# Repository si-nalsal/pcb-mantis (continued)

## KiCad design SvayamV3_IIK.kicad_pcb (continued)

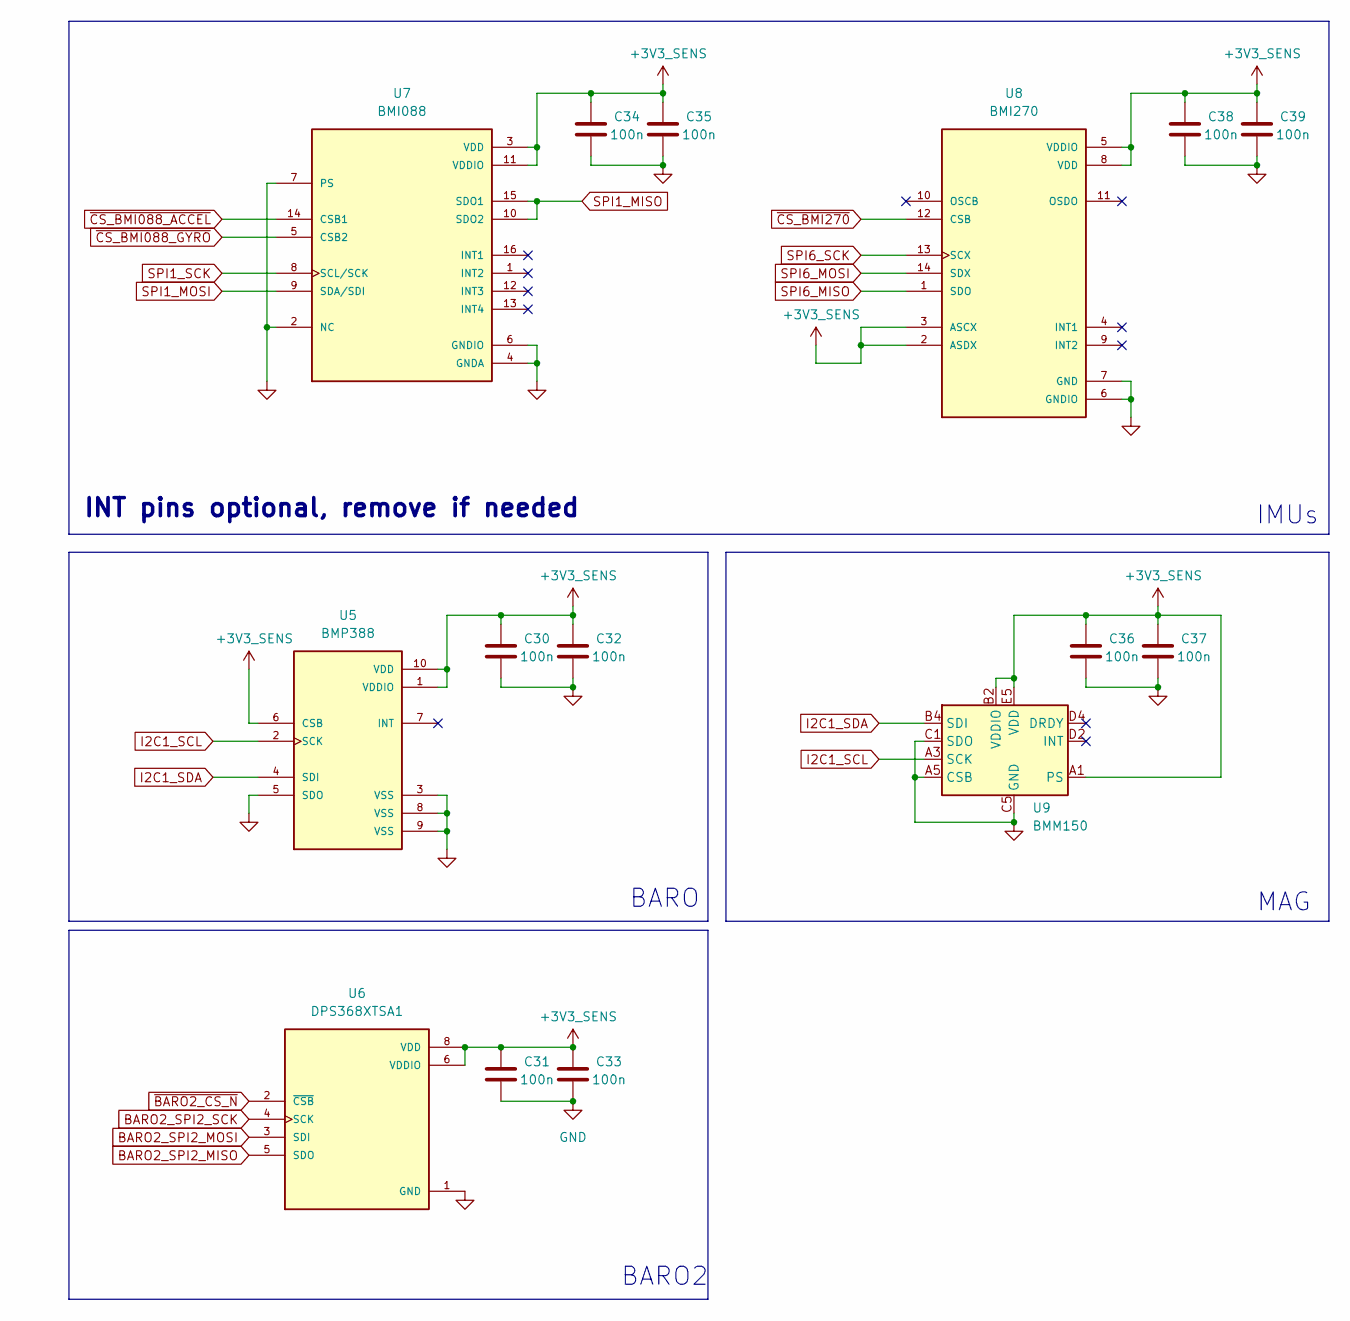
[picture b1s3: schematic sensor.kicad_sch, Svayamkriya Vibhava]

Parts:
C30, C31, C32, C33, C34, C35, C36, C37, C38, C39: 100n; C_0402_1005Metric; MPN CL05B104KB54PNC; LCSC C307331
U5: BMP388; XDCR_BMP388; PARTREV 1.1; LCSC C779278
U6: DPS368XTSA1; XDCR_DPS310XTSA1; MPN DPS368XTSA1; LCSC C3232508
U7: BMI088; PQFN50P450X300X100-16N; MPN BMI088; LCSC C194919
U8: BMI270; XDCR_BMI270; MPN BMI270; LCSC C2836813
U9: BMM150; WLCSP-12_1.56x1.56mm_P0.4mm; MPN BMM150; LCSC C171681

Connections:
+3V3_SENS: C30.1, C31.1, C32.1, C33.1, C34.1, C35.1, C36.1, C37.1, C38.1, C39.1, U5.1 (VDDIO), U5.6 (CSB), U5.10 (VDD), U6.6 (VDDIO), U6.8 (VDD), U7.3 (VDD), U7.11 (VDDIO), U8.2 (ASDX), U8.3 (ASCX), U8.5 (VDDIO), U8.8 (VDD), U9.A1 (PS), U9.B2 (VDDIO), U9.E5 (VDD); also elsewhere on the board
BARO2_SPI2_MISO: U6.5 (SDO); also elsewhere on the board
BARO2_SPI2_MOSI: U6.3 (SDI); also elsewhere on the board
BARO2_SPI2_SCK: U6.4 (SCK); also elsewhere on the board
GND: C30.2, C31.2, C32.2, C33.2, C34.2, C35.2, C36.2, C37.2, C38.2, C39.2, U5.3 (VSS), U5.5 (SDO), U5.8 (VSS), U5.9 (VSS), U6.1 (GND), U6.7 (GND), U7.2 (NC), U7.4 (GNDA), U7.6 (GNDIO), U7.7 (PS), U8.6 (GNDIO), U8.7 (GND), U9.A5 (CSB), U9.C1 (SDO), U9.C5 (GND), U9.E1 (GND), U9.E3 (GND); also elsewhere on the board
I2C1_SCL: U5.2 (SCK), U9.A3 (SCK); also elsewhere on the board
I2C1_SDA: U5.4 (SDI), U9.B4 (SDI); also elsewhere on the board
SPI1_MISO: U7.10 (SDO2), U7.15 (SDO1); also elsewhere on the board
SPI1_MOSI: U7.9 (SDA/SDI); also elsewhere on the board
SPI1_SCK: U7.8 (SCL/SCK); also elsewhere on the board
SPI6_MISO: U8.1 (SDO); also elsewhere on the board
SPI6_MOSI: U8.14 (SDX); also elsewhere on the board
SPI6_SCK: U8.13 (SCX); also elsewhere on the board
~BARO2_CS_N: U6.2 (~CSB); also elsewhere on the board
~CS_BMI088_ACCEL: U7.14 (CSB1); also elsewhere on the board
~CS_BMI088_GYRO: U7.5 (CSB2); also elsewhere on the board
~CS_BMI270: U8.12 (CSB); also elsewhere on the board

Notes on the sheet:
MAG
BARO2
IMUs
BARO
INT pins optional, remove if needed

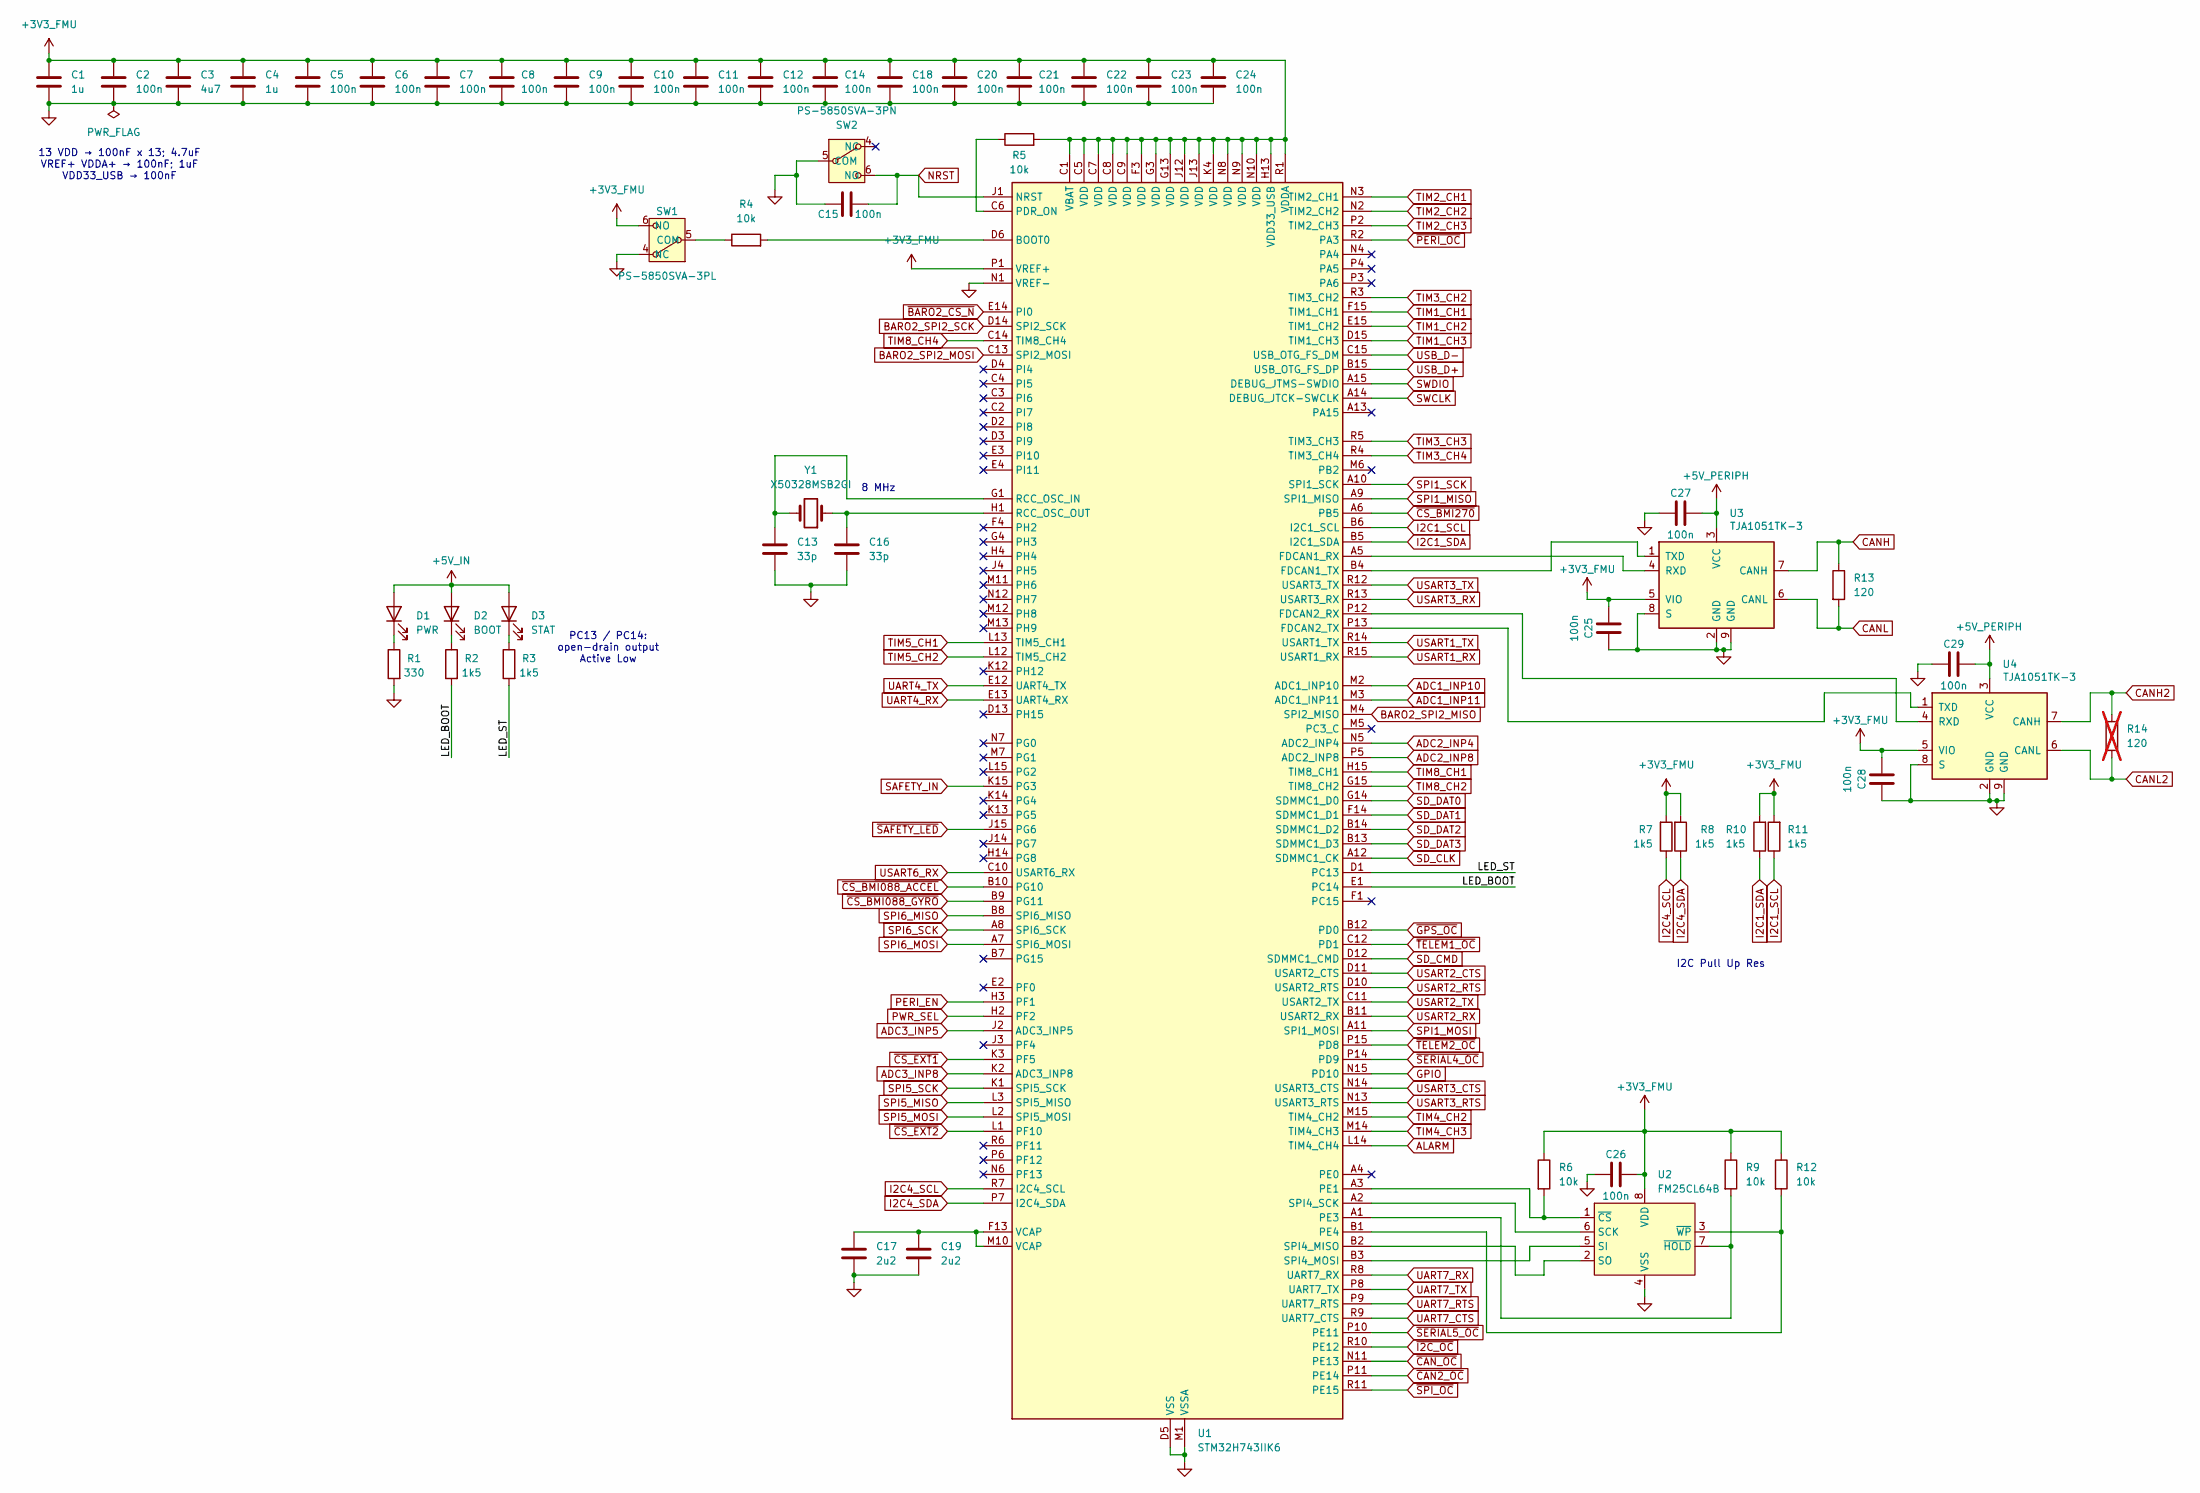
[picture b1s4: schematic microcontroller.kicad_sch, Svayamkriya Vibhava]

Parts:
C1, C4: 1u; C_0603_1608Metric; MPN CL10A105KB8NNNC; LCSC C15849
C2, C5, C6, C7, C8, C9, C10, C11, C12, C14, C15, C18, C20, C21, C22, C23, C24, C25, C26, C27, C28, C29: 100n; C_0402_1005Metric; MPN CL05B104KB54PNC; LCSC C307331
C3: 4u7; C_0603_1608Metric; MPN CL10A475KO8NNNC; LCSC C19666
C13, C16: 33p; C_0402_1005Metric; MPN 0402CG330J500NT; LCSC C1562
C17, C19: 2u2; C_0603_1608Metric; MPN CL10A225KO8NNNC; LCSC C23630
D1: PWR; D_0603_1608Metric; MPN NCD0603R1; LCSC C84263
D2: BOOT; D_0603_1608Metric; MPN NCD0603R1; LCSC C84263
D3: STAT; D_0603_1608Metric; MPN NCD0603R1; LCSC C84263
R1: 330; R_0402_1005Metric; MPN 0402WGF3300TCE; LCSC C25104
R2, R3, R7, R8, R10, R11: 1k5; R_0402_1005Metric; MPN 0402WGF1501TCE; LCSC C25867
R4, R5, R6, R9, R12: 10k; R_0402_1005Metric; MPN 0402WGF1002TCE; LCSC C25744
R13: 120; R_0402_1005Metric; MPN 0402WGF1200TCE; LCSC C25079
R14: 120; R_0402_1005Metric; MPN 0402WGF1200TCE; LCSC C25079; not fitted
SW1: PS-5850SVA-3PL; SW-SMD_G-SWITCH_PS-5850SVX-3PL; MPN PS-5850SVA-3PL; LCSC C5155594
SW2: PS-5850SVA-3PN; SW-SMD_G-SWITCH_PS-5850SVX-3PL; MPN PS-5850SVA-3PN; LCSC C5155595
U1: STM32H743IIK6; UFBGA-201_10x10mm_Layout15x15_P0.65mm; MPN STM32H743IIK6; LCSC C129442
U2: FM25CL64B; SOIC-8_3.9x4.9mm_P1.27mm; MPN FM25CL64B-GTR; LCSC C9830
U3, U4: TJA1051TK-3; DFN-8-1EP_3x3mm_P0.65mm_EP1.55x2.4mm; MPN TJA1051TK/3,118; LCSC C124020
Y1: X50328MSB2GI; Crystal_SMD_5032-2Pin_5.0x3.2mm; MPN X50328MSB2GI; LCSC C115962

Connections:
+3V3_FMU: C1.1, C2.1, C3.1, C4.1, C5.1, C6.1, C7.1, C8.1, C9.1, C10.1, C11.1, C12.1, C14.1, C18.1, C20.1, C21.1, C22.1, C23.1, C24.1, C25.1, C26.2, C28.1, R5.2, R6.1, R7.2, R8.2, R9.1, R10.2, R11.2, R12.1, SW1.6 (NO), U1.C1 (VBAT), U1.C5 (VDD), U1.C7 (VDD), U1.C8 (VDD), U1.C9 (VDD), U1.F3 (VDD), U1.G3 (VDD), U1.G13 (VDD), U1.H13 (VDD33_USB), U1.J12 (VDD), U1.J13 (VDD), U1.K4 (VDD), U1.N8 (VDD), U1.N9 (VDD), U1.N10 (VDD), U1.P1 (VREF+), U1.R1 (VDDA), U2.8 (VDD), U3.5 (VIO), U4.5 (VIO); also elsewhere on the board
+5V_IN: D1.2 (A), D2.2 (A), D3.2 (A); also elsewhere on the board
+5V_PERIPH: C27.2, C29.2, U3.3 (VCC), U4.3 (VCC); also elsewhere on the board
/Microcontroller/LED_BOOT: R2.2, U1.E1 (PC14)
/Microcontroller/LED_ST: R3.2, U1.D1 (PC13)
ADC1_INP10: U1.M2 (ADC1_INP10); also elsewhere on the board
ADC1_INP11: U1.M3 (ADC1_INP11); also elsewhere on the board
ADC2_INP4: U1.N5 (ADC2_INP4); also elsewhere on the board
ADC2_INP8: U1.P5 (ADC2_INP8); also elsewhere on the board
ADC3_INP5: U1.J2 (ADC3_INP5); also elsewhere on the board
ADC3_INP8: U1.K2 (ADC3_INP8); also elsewhere on the board
ALARM: U1.L14 (TIM4_CH4); also elsewhere on the board
BARO2_SPI2_MISO: U1.M4 (SPI2_MISO); also elsewhere on the board
BARO2_SPI2_MOSI: U1.C13 (SPI2_MOSI); also elsewhere on the board
BARO2_SPI2_SCK: U1.D14 (SPI2_SCK); also elsewhere on the board
CANH: R13.1, U3.7 (CANH); also elsewhere on the board
CANH2: R14.1, U4.7 (CANH); also elsewhere on the board
CANL: R13.2, U3.6 (CANL); also elsewhere on the board
CANL2: R14.2, U4.6 (CANL); also elsewhere on the board
GND: C1.2, C2.2, C3.2, C4.2, C5.2, C6.2, C7.2, C8.2, C9.2, C10.2, C11.2, C12.2, C13.2, C14.2, C15.1, C16.2, C17.2, C18.2, C19.2, C20.2, C21.2, C22.2, C23.2, C24.2, C25.2, C26.1, C27.1, C28.2, C29.1, R1.2, SW1.4 (NC), SW2.5 (COM), U1.D5 (VSS), U1.D7 (VSS), U1.D8 (VSS), U1.D9 (VSS), U1.F2 (VSS), U1.F6 (VSS), U1.F7 (VSS), U1.F8 (VSS), U1.F9 (VSS), U1.F10 (VSS), U1.F12 (VSS), U1.G2 (VSS), U1.G6 (VSS), U1.G7 (VSS), U1.G8 (VSS), U1.G9 (VSS), U1.G10 (VSS), U1.G12 (VSS), U1.H6 (VSS), U1.H7 (VSS), U1.H8 (VSS), U1.H9 (VSS), U1.H10 (VSS), U1.H12 (VSS), U1.J6 (VSS), U1.J7 (VSS), U1.J8 (VSS), U1.J9 (VSS), U1.J10 (VSS), U1.K6 (VSS), U1.K7 (VSS), U1.K8 (VSS), U1.K9 (VSS), U1.K10 (VSS), U1.L4 (VSS), U1.M1 (VSSA), U1.M8 (VSS), U1.M9 (VSS), U1.N1 (VREF-), U2.4 (VSS), U3.2 (GND), U3.8 (S), U3.9 (GND), U4.2 (GND), U4.8 (S), U4.9 (GND); also elsewhere on the board
GPIO: U1.N15 (PD10); also elsewhere on the board
I2C1_SCL: R11.1, U1.B6 (I2C1_SCL); also elsewhere on the board
I2C1_SDA: R10.1, U1.B5 (I2C1_SDA); also elsewhere on the board
I2C4_SCL: R7.1, U1.R7 (I2C4_SCL); also elsewhere on the board
I2C4_SDA: R8.1, U1.P7 (I2C4_SDA); also elsewhere on the board
NRST: C15.2, SW2.6 (NO), U1.J1 (NRST); also elsewhere on the board
unnamed: C17.1, C19.1, U1.F13 (VCAP), U1.M10 (VCAP)
unnamed: D1.1 (K), R1.1
unnamed: D2.1 (K), R2.1
unnamed: D3.1 (K), R3.1
unnamed: R4.1, SW1.5 (COM)
unnamed: R4.2, U1.D6 (BOOT0)
unnamed: U1.A5 (FDCAN1_RX), U3.4 (RXD)
unnamed: U1.B4 (FDCAN1_TX), U3.1 (TXD)
unnamed: U1.P12 (FDCAN2_RX), U4.4 (RXD)
unnamed: U1.P13 (FDCAN2_TX), U4.1 (TXD)
unnamed: R5.1, U1.C6 (PDR_ON)
unnamed: R6.2, U1.A3 (PE1), U2.1 (~CS)
unnamed: U1.A2 (SPI4_SCK), U2.6 (SCK)
unnamed: R9.2, U1.A1 (PE3), U2.7 (~HOLD)
unnamed: R12.2, U1.B1 (PE4), U2.3 (~WP)
unnamed: U1.B2 (SPI4_MISO), U2.2 (SO)
unnamed: U1.B3 (SPI4_MOSI), U2.5 (SI)
unnamed: C13.1, U1.G1 (RCC_OSC_IN), Y1.2
unnamed: C16.1, U1.H1 (RCC_OSC_OUT), Y1.1
PERI_EN: U1.H3 (PF1); also elsewhere on the board
PWR_SEL: U1.H2 (PF2); also elsewhere on the board
SAFETY_IN: U1.K15 (PG3); also elsewhere on the board
SD_CLK: U1.A12 (SDMMC1_CK); also elsewhere on the board
SD_CMD: U1.D12 (SDMMC1_CMD); also elsewhere on the board
SD_DAT0: U1.G14 (SDMMC1_D0); also elsewhere on the board
SD_DAT1: U1.F14 (SDMMC1_D1); also elsewhere on the board
SD_DAT2: U1.B14 (SDMMC1_D2); also elsewhere on the board
SD_DAT3: U1.B13 (SDMMC1_D3); also elsewhere on the board
SPI1_MISO: U1.A9 (SPI1_MISO); also elsewhere on the board
SPI1_MOSI: U1.A11 (SPI1_MOSI); also elsewhere on the board
SPI1_SCK: U1.A10 (SPI1_SCK); also elsewhere on the board
SPI5_MISO: U1.L3 (SPI5_MISO); also elsewhere on the board
SPI5_MOSI: U1.L2 (SPI5_MOSI); also elsewhere on the board
SPI5_SCK: U1.K1 (SPI5_SCK); also elsewhere on the board
SPI6_MISO: U1.B8 (SPI6_MISO); also elsewhere on the board
SPI6_MOSI: U1.A7 (SPI6_MOSI); also elsewhere on the board
SPI6_SCK: U1.A8 (SPI6_SCK); also elsewhere on the board
SWCLK: U1.A14 (DEBUG_JTCK-SWCLK); also elsewhere on the board
SWDIO: U1.A15 (DEBUG_JTMS-SWDIO); also elsewhere on the board
TIM1_CH1: U1.F15 (TIM1_CH1); also elsewhere on the board
TIM1_CH2: U1.E15 (TIM1_CH2); also elsewhere on the board
TIM1_CH3: U1.D15 (TIM1_CH3); also elsewhere on the board
TIM2_CH1: U1.N3 (TIM2_CH1); also elsewhere on the board
TIM2_CH2: U1.N2 (TIM2_CH2); also elsewhere on the board
TIM2_CH3: U1.P2 (TIM2_CH3); also elsewhere on the board
TIM3_CH2: U1.R3 (TIM3_CH2); also elsewhere on the board
TIM3_CH3: U1.R5 (TIM3_CH3); also elsewhere on the board
TIM3_CH4: U1.R4 (TIM3_CH4); also elsewhere on the board
TIM4_CH2: U1.M15 (TIM4_CH2); also elsewhere on the board
TIM4_CH3: U1.M14 (TIM4_CH3); also elsewhere on the board
TIM5_CH1: U1.L13 (TIM5_CH1); also elsewhere on the board
TIM5_CH2: U1.L12 (TIM5_CH2); also elsewhere on the board
TIM8_CH1: U1.H15 (TIM8_CH1); also elsewhere on the board
TIM8_CH2: U1.G15 (TIM8_CH2); also elsewhere on the board
TIM8_CH4: U1.C14 (TIM8_CH4); also elsewhere on the board
UART4_RX: U1.E13 (UART4_RX); also elsewhere on the board
UART4_TX: U1.E12 (UART4_TX); also elsewhere on the board
UART7_CTS: U1.R9 (UART7_CTS); also elsewhere on the board
UART7_RTS: U1.P9 (UART7_RTS); also elsewhere on the board
UART7_RX: U1.R8 (UART7_RX); also elsewhere on the board
UART7_TX: U1.P8 (UART7_TX); also elsewhere on the board
USART1_RX: U1.R15 (USART1_RX); also elsewhere on the board
USART1_TX: U1.R14 (USART1_TX); also elsewhere on the board
USART2_CTS: U1.D11 (USART2_CTS); also elsewhere on the board
USART2_RTS: U1.D10 (USART2_RTS); also elsewhere on the board
USART2_RX: U1.B11 (USART2_RX); also elsewhere on the board
USART2_TX: U1.C11 (USART2_TX); also elsewhere on the board
USART3_CTS: U1.N14 (USART3_CTS); also elsewhere on the board
USART3_RTS: U1.N13 (USART3_RTS); also elsewhere on the board
USART3_RX: U1.R13 (USART3_RX); also elsewhere on the board
USART3_TX: U1.R12 (USART3_TX); also elsewhere on the board
USART6_RX: U1.C10 (USART6_RX); also elsewhere on the board
USB_D+: U1.B15 (USB_OTG_FS_DP); also elsewhere on the board
USB_D-: U1.C15 (USB_OTG_FS_DM); also elsewhere on the board
~BARO2_CS_N: U1.E14 (PI0); also elsewhere on the board
~CAN2_OC: U1.P11 (PE14); also elsewhere on the board
~CAN_OC: U1.N11 (PE13); also elsewhere on the board
~CS_BMI088_ACCEL: U1.B10 (PG10); also elsewhere on the board
~CS_BMI088_GYRO: U1.B9 (PG11); also elsewhere on the board
~CS_BMI270: U1.A6 (PB5); also elsewhere on the board
~CS_EXT1: U1.K3 (PF5); also elsewhere on the board
~CS_EXT2: U1.L1 (PF10); also elsewhere on the board
~GPS_OC: U1.B12 (PD0); also elsewhere on the board
~I2C_OC: U1.R10 (PE12); also elsewhere on the board
~PERI_OC: U1.R2 (PA3); also elsewhere on the board
~SAFETY_LED: U1.J15 (PG6); also elsewhere on the board
~SERIAL4_OC: U1.P14 (PD9); also elsewhere on the board
~SERIAL5_OC: U1.P10 (PE11); also elsewhere on the board
~SPI_OC: U1.R11 (PE15); also elsewhere on the board
~TELEM1_OC: U1.C12 (PD1); also elsewhere on the board
~TELEM2_OC: U1.P15 (PD8); also elsewhere on the board

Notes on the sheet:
8 MHz
I2C Pull Up Res
13 VDD → 100nF x 13; 4.7uF VREF+ VDDA+ → 100nF; 1uF VDD33_USB → 100nF
PC13 / PC14: open-drain output Active Low

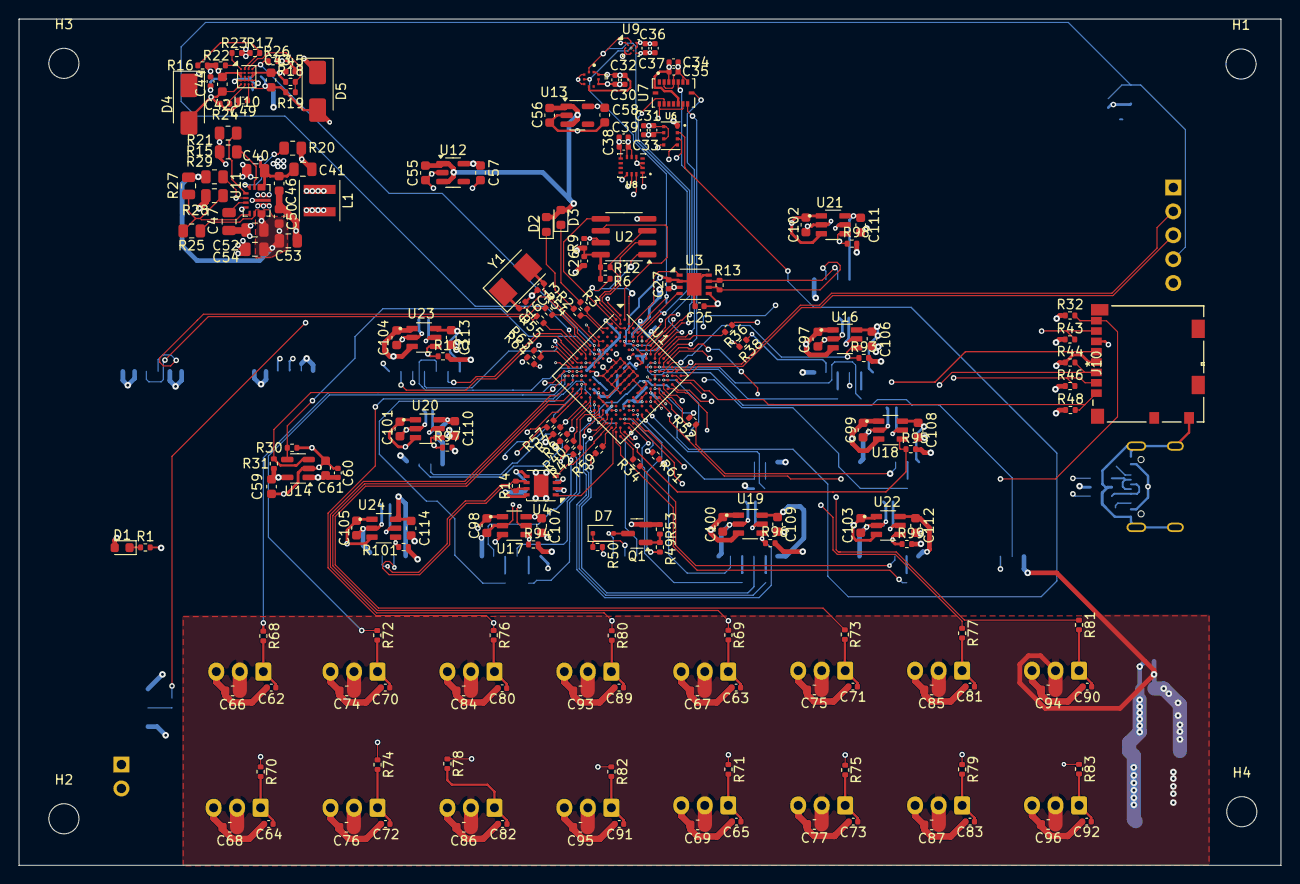
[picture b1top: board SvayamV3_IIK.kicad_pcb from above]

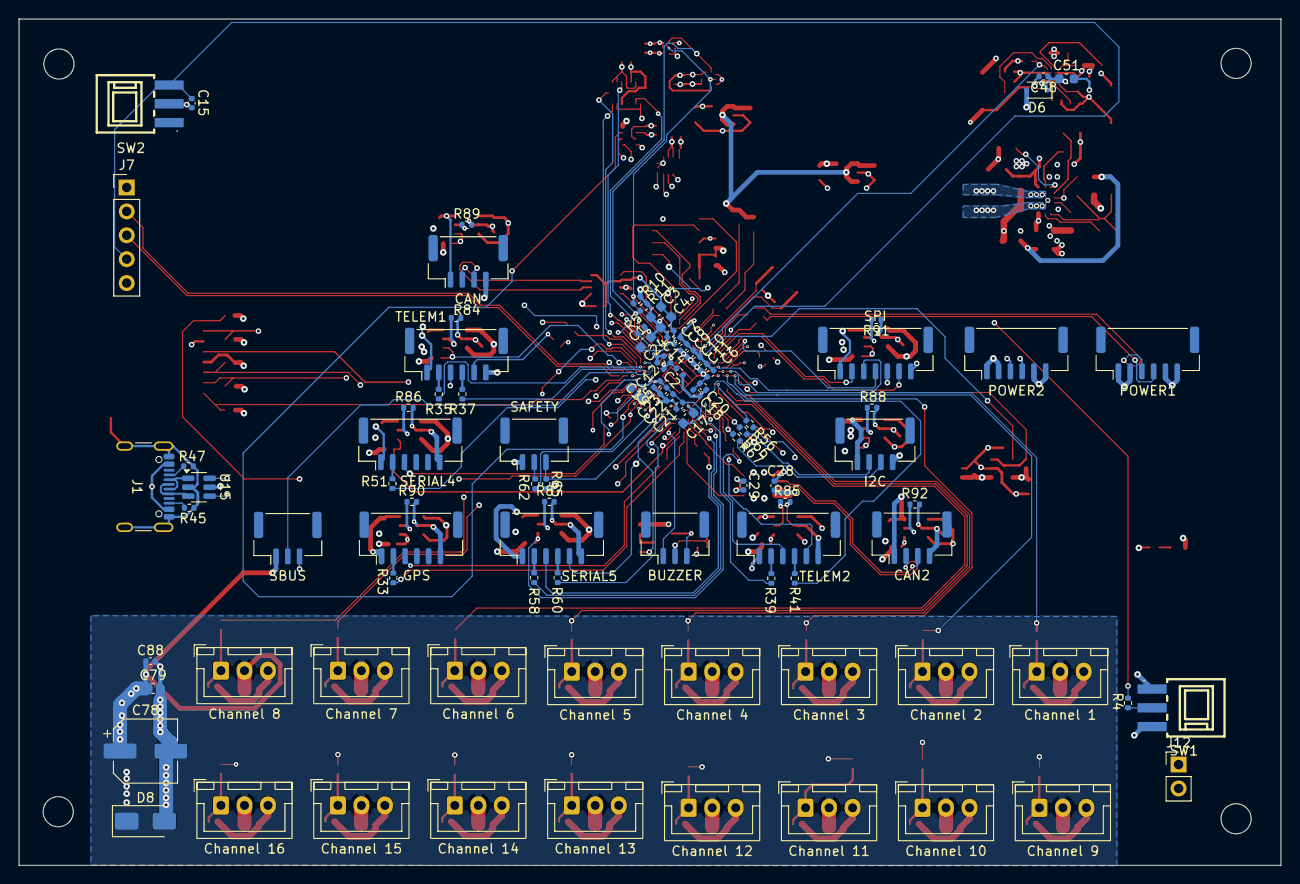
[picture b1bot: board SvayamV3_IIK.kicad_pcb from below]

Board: 6 copper layers, 134.1 x 90.0 mm, 290 parts (95 on the bottom side), 203 nets.

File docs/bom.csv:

"Refs","Value","Footprint","MPN","LCSC"
"C1,C4,C59,C66-C69,C74-C77,C79,C84-C87,C93-C114","1u","Capacitor_SMD:C_0603_1608Metric","CL10A105KB8NNNC",""
"C2,C5-C12,C14,C15,C18,C20-C39,C44,C45,C48,C49,C60,C62-C65,C70-C73,C80-C83,C88-C92","100n","Capacitor_SMD:C_0402_1005Metric","CL05B104KB54PNC",""
"C3,C42,C43,C55-C58","4u7","Capacitor_SMD:C_0603_1608Metric","CL10A475KO8NNNC",""
"C13,C16","33p","Capacitor_SMD:C_0402_1005Metric","0402CG330J500NT",""
"C17,C19","2u2","Capacitor_SMD:C_0603_1608Metric","CL10A225KO8NNNC",""
"C40,C41","10u","Capacitor_SMD:C_0805_2012Metric","",""
"C46,C50,C51,C61","10u","Capacitor_SMD:C_0603_1608Metric","CL10A106MA8NRNC",""
"C47","100n","Capacitor_SMD:C_0805_2012Metric","",""
"C52-C54","22u","Capacitor_SMD:C_0805_2012Metric","",""
"C78","220u","Capacitor_SMD:CP_Elec_6.3x7.7","",""
"D1","PWR","Diode_SMD:D_0603_1608Metric","NCD0603R1",""
"D2","BOOT","Diode_SMD:D_0603_1608Metric","NCD0603R1",""
"D3","STAT","Diode_SMD:D_0603_1608Metric","NCD0603R1",""
"D4,D5,D8","SMAJ6.0A","Diode_SMD:D_SMA","",""
"D6,D7","PMEG1030EJ,115","Diode_SMD:D_SOD-323F","PMEG1030EJ,115",""
"J1","USB_C_Receptacle_USB2.0_16P","easyeda2kicad:USB-C-SMD_TYPE-C16PIN","TYPE-C16PIN",""
"J2","GPS","Connector_JST:JST_GH_BM06B-GHS-TBT_1x06-1MP_P1.25mm_Vertical","",""
"J3","SPI","Connector_JST:JST_GH_BM07B-GHS-TBT_1x07-1MP_P1.25mm_Vertical","",""
"J4","TELEM1","Connector_JST:JST_GH_BM06B-GHS-TBT_1x06-1MP_P1.25mm_Vertical","",""
"J5","TELEM2","Connector_JST:JST_GH_BM06B-GHS-TBT_1x06-1MP_P1.25mm_Vertical","",""
"J6","SBUS","Connector_JST:JST_GH_BM03B-GHS-TBT_1x03-1MP_P1.25mm_Vertical","",""
"J7","Conn_01x05_Pin","Connector_PinHeader_2.54mm:PinHeader_1x05_P2.54mm_Vertical","",""
"J8","SERIAL4","Connector_JST:JST_GH_BM06B-GHS-TBT_1x06-1MP_P1.25mm_Vertical","",""
"J9","POWER1","Connector_JST:JST_GH_BM06B-GHS-TBT_1x06-1MP_P1.25mm_Vertical","",""
"J10","Micro_SD_Card_Det1","Svayam:104031-0811_MOL","1040310811",""
"J11","BUZZER","Connector_JST:JST_GH_BM03B-GHS-TBT_1x03-1MP_P1.25mm_Vertical","",""
"J12","ADC","Connector_PinHeader_2.54mm:PinHeader_1x02_P2.54mm_Vertical","",""
"J13","CAN","Connector_JST:JST_GH_BM04B-GHS-TBT_1x04-1MP_P1.25mm_Vertical","",""
"J14","SERIAL5","Connector_JST:JST_GH_BM06B-GHS-TBT_1x06-1MP_P1.25mm_Vertical","",""
"J15","SAFETY","Connector_JST:JST_GH_BM03B-GHS-TBT_1x03-1MP_P1.25mm_Vertical","",""
"J16","POWER2","Connector_JST:JST_GH_BM06B-GHS-TBT_1x06-1MP_P1.25mm_Vertical","",""
"J17","I2C","Connector_JST:JST_GH_BM04B-GHS-TBT_1x04-1MP_P1.25mm_Vertical","",""
"J18","CAN2","Connector_JST:JST_GH_BM04B-GHS-TBT_1x04-1MP_P1.25mm_Vertical","",""
"J19","Channel 1","Connector_JST:JST_XH_B3B-XH-A_1x03_P2.50mm_Vertical","",""
"J20","Channel 5","Connector_JST:JST_XH_B3B-XH-A_1x03_P2.50mm_Vertical","",""
"J21","Channel 9","Connector_JST:JST_XH_B3B-XH-A_1x03_P2.50mm_Vertical","",""
"J22","Channel 13","Connector_JST:JST_XH_B3B-XH-A_1x03_P2.50mm_Vertical","",""
"J23","Channel 2","Connector_JST:JST_XH_B3B-XH-A_1x03_P2.50mm_Vertical","",""
"J24","Channel 6","Connector_JST:JST_XH_B3B-XH-A_1x03_P2.50mm_Vertical","",""
"J25","Channel 10","Connector_JST:JST_XH_B3B-XH-A_1x03_P2.50mm_Vertical","",""
"J26","Channel 14","Connector_JST:JST_XH_B3B-XH-A_1x03_P2.50mm_Vertical","",""
"J27","Channel 3","Connector_JST:JST_XH_B3B-XH-A_1x03_P2.50mm_Vertical","",""
"J28","Channel 7","Connector_JST:JST_XH_B3B-XH-A_1x03_P2.50mm_Vertical","",""
"J29","Channel 11","Connector_JST:JST_XH_B3B-XH-A_1x03_P2.50mm_Vertical","",""
"J30","Channel 15","Connector_JST:JST_XH_B3B-XH-A_1x03_P2.50mm_Vertical","",""
"J31","Channel 4","Connector_JST:JST_XH_B3B-XH-A_1x03_P2.50mm_Vertical","",""
"J32","Channel 8","Connector_JST:JST_XH_B3B-XH-A_1x03_P2.50mm_Vertical","",""
"J33","Channel 12","Connector_JST:JST_XH_B3B-XH-A_1x03_P2.50mm_Vertical","",""
"J34","Channel 16","Connector_JST:JST_XH_B3B-XH-A_1x03_P2.50mm_Vertical","",""
"L1","1.5u","Svayam:L_Coilcraft_XxL4020","",""
"Q1","AO3400A","Package_TO_SOT_SMD:SOT-23","AO3400A",""
"R1","330","Resistor_SMD:R_0402_1005Metric","0402WGF3300TCE",""
"R2,R3,R7,R8,R10,R11,R65","1k5","Resistor_SMD:R_0402_1005Metric","0402WGF1501TCE",""
"R4-R6,R9,R12,R31,R53-R57,R63,R64","10k","Resistor_SMD:R_0402_1005Metric","0402WGF1002TCE",""
"R13,R14,R33-R42,R51,R52,R58-R61,R66-R83","120","Resistor_SMD:R_0402_1005Metric","0402WGF1200TCE",""
"R15,R21","10k","Resistor_SMD:R_0805_2012Metric","",""
"R16,R18","22k","Resistor_SMD:R_0402_1005Metric","0402WGF2202TCE",""
"R17,R19,R23,R45,R47,R49","5k1","Resistor_SMD:R_0402_1005Metric","0402WGF5101TCE",""
"R20,R25,R29","100k","Resistor_SMD:R_0805_2012Metric","",""
"R22","15k","Resistor_SMD:R_0402_1005Metric","0402WGF1502TCE",""
"R24,R84,R85","33k","Resistor_SMD:R_0402_1005Metric","0402WGF3302TCE",""
"R26,R30","100k","Resistor_SMD:R_0402_1005Metric","0402WGF1003TCE",""
"R27","68k","Resistor_SMD:R_0805_2012Metric","",""
"R28","13k","Resistor_SMD:R_0805_2012Metric","",""
"R32,R43,R44,R46,R48","51k","Resistor_SMD:R_0402_1005Metric","0402WGF5102TCE",""
"R50","10","Resistor_SMD:R_0402_1005Metric","0402WGF100JTCE",""
"R62","49.9","Resistor_SMD:R_0402_1005Metric","0402WGF499JTCE",""
"R86,R87","75k","Resistor_SMD:R_0402_1005Metric","",""
"R88,R91","110k","Resistor_SMD:R_0402_1005Metric","",""
"R89,R92","47k","Resistor_SMD:R_0402_1005Metric","",""
"R90","56k","Resistor_SMD:R_0402_1005Metric","",""
"SW1","SK-3296S-01-L3","easyeda2kicad:SW-SMD_SK-3296S-01-L3","SK-3296S-01-L3",""
"SW2","TS-1010A-B","easyeda2kicad:SW-SMD_TS-1010A-B","TS-1010A-B",""
"U1","STM32H743IIK6","Package_BGA:UFBGA-201_10x10mm_Layout15x15_P0.65mm","STM32H743IIK6",""
"U2","FM25CL64B","Package_SO:SOIC-8_3.9x4.9mm_P1.27mm","FM25CL64B-GTR",""
"U3,U4","TJA1051TK-3","Package_DFN_QFN:DFN-8-1EP_3x3mm_P0.65mm_EP1.55x2.4mm","TJA1051TK/3,118",""
"U5","BMP388","Svayam:XDCR_BMP388","BMP388",""
"U6","DPS310XTSA1","Svayam:XDCR_DPS310XTSA1","",""
"U7","BMI088","Svayam:PQFN50P450X300X100-16N","BMI088",""
"U8","BMI270","Svayam:XDCR_BMI270","BMI270",""
"U9","BMM150","Package_CSP:WLCSP-12_1.56x1.56mm_P0.4mm","BMM150",""
"U10","TPS2120YFPR","Package_BGA:Texas_YFP0020_DSBGA-20_1.588x1.988mm_Layout4x5_P0.4mm","TPS2120YFPR",""
"U11","TPS63070","Svayam:VQFN-HR-15","",""
"U12,U13","RT9080-33GJ5","Package_TO_SOT_SMD:TSOT-23-5","RT9080-33GJ5",""
"U14","AP22804AW5","Package_TO_SOT_SMD:SOT-23-5","AP22804AW5-7",""
"U15","USBLC6-2SC6","Package_TO_SOT_SMD:SOT-23-6","USBLC6-2SC6",""
"U16-U24","TPS2553DBVT","Svayam:SOT95P280X145-6N","",""
"Y1","X50328MSB2GI","Crystal:Crystal_SMD_5032-2Pin_5.0x3.2mm","X50328MSB2GI",""
